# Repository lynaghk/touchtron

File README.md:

# Touchtron

Misc. experiments with Rust + USB, Kevin making a touchpad.

See [background + video demo](https://kevinlynagh.com/touchpad/).

The [firmware-f0](firmware-f0/) is the fully-baked code running on the PCB ([schematic PDF](pcb/submitted_2020_05_26/touchtron.pdf)).

This was a personal research project that I'm sharing in case it's helpful for others playing with touchpads, embedded Rust, etc.

## MacOS Setup 

```
#for stm32f0 (kevin custom board)
rustup target add thumbv6m-none-eabi 

#for stm32f1 (blue pill board)
rustup target add thumbv7m-none-eabi

pip install numpy matplotlib scipy opencv-python

pip install pyusb
brew install libusb 
```

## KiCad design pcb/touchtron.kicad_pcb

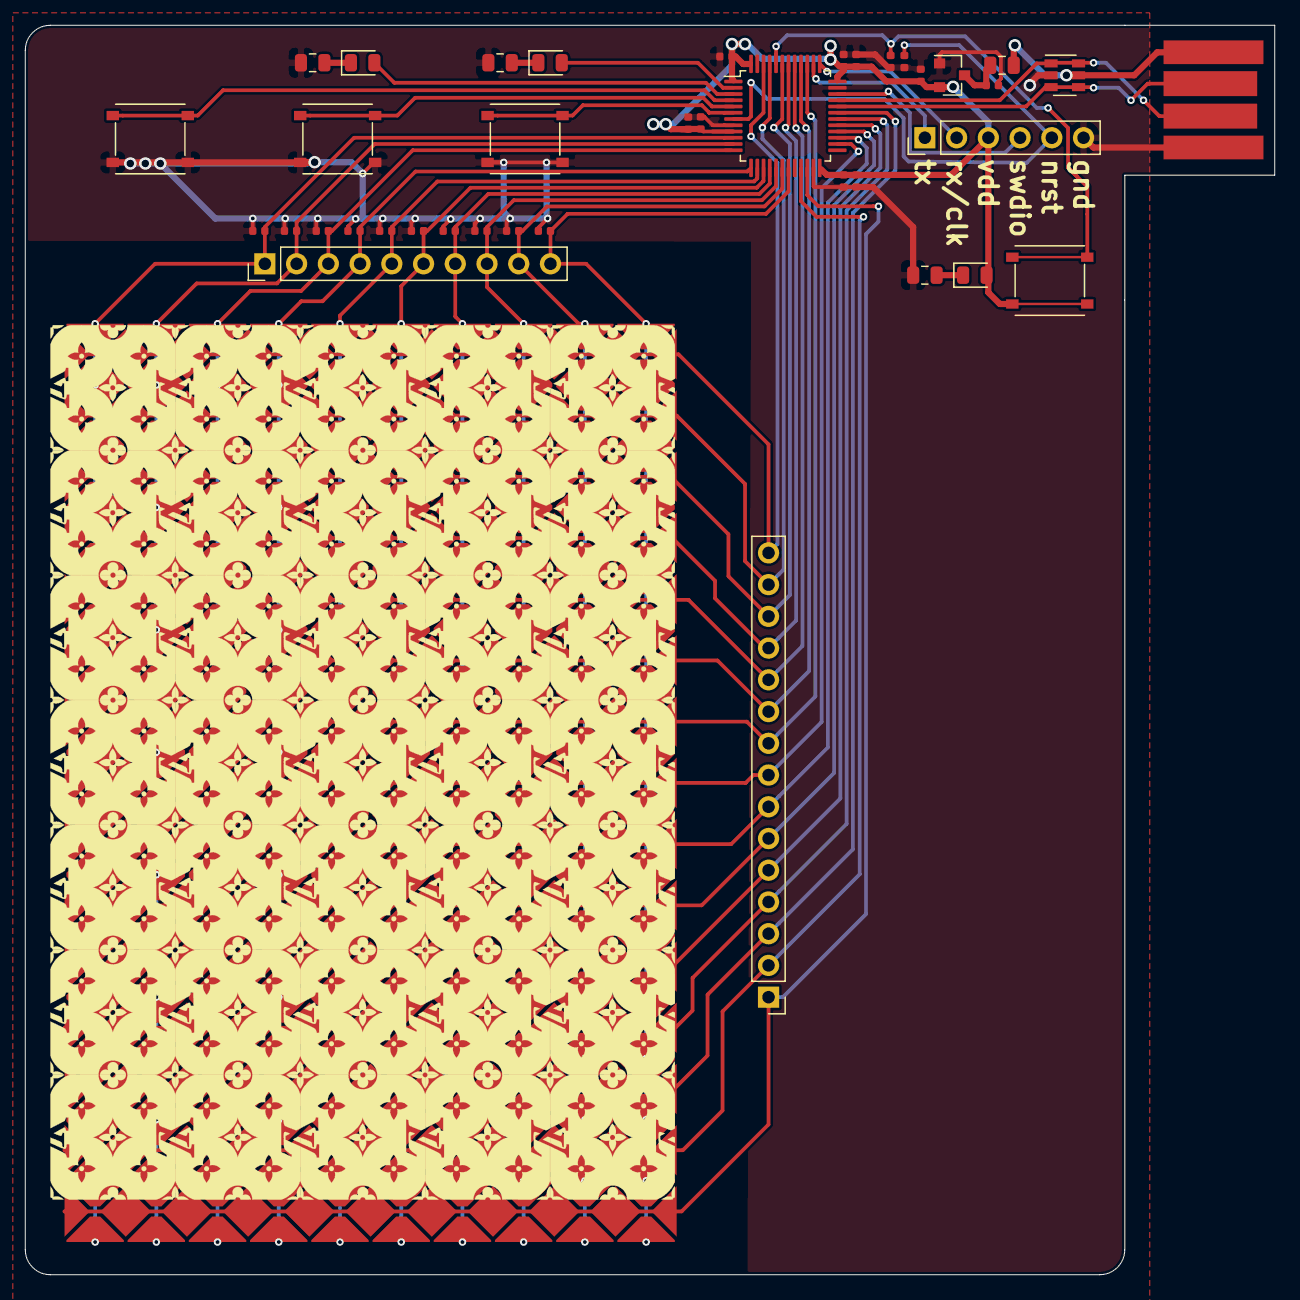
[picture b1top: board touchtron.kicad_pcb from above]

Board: 2 copper layers, 100.0 x 100.0 mm, 40 parts (0 on the bottom side), 44 nets.

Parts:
C1, C2, C6: 1u; C_0402_1005Metric
C3: 10n; C_0402_1005Metric
C4, C5, C7, C10: 100n; C_0402_1005Metric
C8, C9: 4.7u; C_0402_1005Metric
D1, D2: White LED; LED_0805_2012Metric
D3: Green LED; LED_0805_2012Metric
FB1: Ferrite_Bead; C_0805_2012Metric
J1: USB_A; usb_a_edge_connector
J2: Conn_01x06_Female; PinHeader_1x06_P2.54mm_Vertical
J3: Conn_01x15_Female; PinHeader_1x15_P2.54mm_Vertical
J4: Conn_01x10_Female; PinHeader_1x10_P2.54mm_Vertical
R1, R2, R3, R4, R5, R6, R7, R8, R9, R11: 100k; R_0402_1005Metric
R10: 5.1k; R_0402_1005Metric
R12, R13, R14: 330; R_0805_2012Metric
SW1, SW2, SW3, SW4: TS-1187A-C-D-B; TS-1187A
T1: Touchpad_10x15; touchpad_49_10_15
U1: XC6206P332MR; SOT-23
U2: USBLC6-2SC6; SOT-23-6
U3: STM32F072CBT6; LQFP-48_7x7mm_P0.5mm

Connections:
GND: C1.2, C2.2, C3.2, C4.2, C5.2, C6.2, C7.2, C8.2, C9.2, C10.2, J1.4, J2.6, R1.2, R2.2, R3.2, R4.2, R5.2, R6.2, R7.2, R8.2, R9.2, R10.2, R11.2, R12.1, R13.1, R14.1, SW2.2, SW3.2, SW4.2, U1.1, U2.2, U3.8, U3.23, U3.35, U3.47
NRST: C10.1, J2.5, U3.7
unnamed: C1.1, FB1.1, U1.3
unnamed: D1.1, R12.2
unnamed: D2.1, R13.2
unnamed: D3.1, R14.2
SWDIO: J2.4, U3.34
USB_D+: J1.3, U2.1, U2.6, U3.33
USB_D-: J1.2, U2.3, U2.4, U3.32
VBUS: FB1.2, J1.1, U2.5
VDD: C2.1, C3.1, C4.1, C5.1, C6.1, C7.1, C8.1, C9.1, D3.2, J2.3, SW1.1, U1.2, U3.1, U3.9, U3.24, U3.36, U3.48
a0: J4.1, R1.1, T1.10, U3.10
a1: J4.2, R2.1, T1.9, U3.11
a2: J4.3, R3.1, T1.8, U3.12
a3: J4.4, R4.1, T1.7, U3.13
a4: J4.5, R5.1, T1.6, U3.14
a5: J4.6, R6.1, T1.5, U3.15
a6: J4.7, R7.1, T1.4, U3.16
a7: J4.8, R8.1, T1.3, U3.17
a8: J4.9, R9.1, T1.2, U3.18
a9: J4.10, R11.1, T1.1, U3.19
b0: J3.1, T1.25, U3.22
b1: J3.2, T1.24, U3.21
b2: J3.3, T1.23, U3.31
b3: J3.4, T1.22, U3.30
b4: J3.5, T1.21, U3.29
b5: J3.6, T1.20, U3.28
b6: J3.7, T1.19, U3.27
b7: J3.8, T1.18, U3.26
b8: J3.9, T1.17, U3.39
b9: J3.10, T1.16, U3.40
b10: J3.11, T1.15, U3.41
b11: J3.12, T1.14, U3.42
b12: J3.13, T1.13, U3.43
b13: J3.14, T1.12, U3.45
b14: J3.15, T1.11, U3.46
boot0: R10.1, SW1.2, U3.44
led0: D1.2, U3.3
led1: D2.2, U3.2
sw0: SW2.1, U3.4
sw1: SW3.1, U3.5
sw2: SW4.1, U3.6
swclk_usart2_tx: J2.2, U3.37
usart2_rx: J2.1, U3.38

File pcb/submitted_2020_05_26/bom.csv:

"Comment","Designator","Footprint","LCSC Part #"
"Ferrite_Bead","FB1","805","C1015"
"10n","C3","402","C15195"
"100n","C4,C5,C7,C10","402","C1525"
"330","R12,R13,R14","805","C17630"
"Green LED","D3","805","C2297"
"4.7u","C8,C9","402","C23733"
"100k","R1,R2,R3,R4,R5,R6,R7,R8,R9,R11","402","C25741"
"5.1k","R10","402","C25905"
"TS-1187A-C-D-B","SW1,SW2,SW3,SW4","SMD-SW-4_5.1x5.1x2.0","C318888"
"White LED","D1,D2","805","C34499"
"1u","C1,C2,C6","402","C52923"
"XC6206P332MR","U1","SOT-23-3L","C5446"
"USBLC6-2SC6","U2","SOT-23-6L","C7519"
"STM32F072CBT6","U3","LQFP-48_7.0x7.0x0.5P","C81720"

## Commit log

2020-06-03 Factor touchtron bits out to their own repo so I can share with Jake and Oskar.
2020-06-04 changes for stm32 discovery board
2020-06-04 WIP: midi controller on blue pill; Allllmost have working button interrupt.
2020-06-05 rtfm-ify stm32f0xx version
2020-06-06 user button toggles led for discovery board
2020-06-06 Interrupt to toggle led working.
2020-06-06 WIP: Report more complex data over USB
2020-06-07 WIP: fighting with rust lifetimes.
2020-06-07 Reorganize to be clearer about the 3 boards we have in play: f0 discovery, f103 blue pill, and f0 touchtron.
2020-06-08 Get USB data reporting working on touchtron board.
2020-06-08 Add types for touchtron hardware; WIP trying to read analog inputs.
2020-06-08 Read ADC successfully.
2020-06-08 USB reporter tidy.
2020-06-09 WIP: ADC.
2020-06-09 Plot ADC heatmap measuring 3 pins, channels always on. 160--190 FPS.
2020-06-10 WIP: other output pins.
2020-06-10 WIP: types types types.
2020-06-10 WIP: Scan columns; report over USB.
    Running into some kind of USB timeout issue; I don't think the interrupts are setup properly.
2020-06-12 Scanning columns over USB seems to work alright.
2020-06-14 Notes.
2020-06-19 WIP: scan PWM periods, report over USB (untested)
2020-06-19 WIP: very low capacitive touch signal, seems quite noisy.
    Even when physically connecting pins, a few frames are displayed full of noise.
    But that doesn't make sense; must be a logic error somewhere.
2020-06-20 USB timing notes.
2020-06-20 More USB experiments. Think I need to just write ADC sampling code myself to average signal over time.
2020-06-21 Continuous scanning of ADC (untested).
2020-06-22 Can't use continous mode because we can't service interrupts fast enough (contention w/ USB interrupt).
    Instead, chain row sampling together in the interrupt.
2020-06-23 Try to improve SNR by making sure columns go low (rather than float); Python data smoothing.
2020-06-23 animation perf tests; use opencv2.
2020-06-24 OpenCV blob detection for rough finger location detection.
2020-06-25 touchpad scope measurement notes.
2021-02-08 Add PCB-related files.
2021-02-08 Reorganize files for public release.
2021-02-08 Add schematic PDF.
2021-02-19 Add demo image.
